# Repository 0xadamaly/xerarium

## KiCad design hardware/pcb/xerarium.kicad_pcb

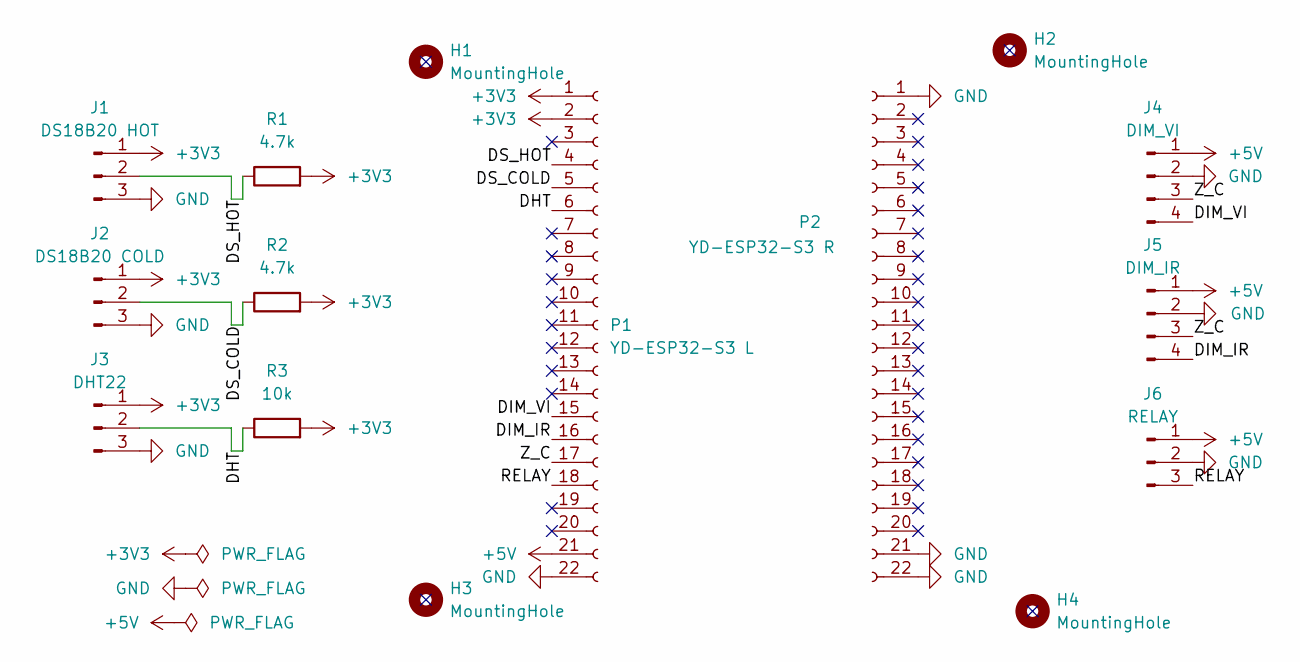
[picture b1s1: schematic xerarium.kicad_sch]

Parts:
H1, H2, H3, H4: MountingHole; MountingHole_3.2mm_M3
J1: DS18B20 HOT; JST_PH_S3B-PH-K_1x03_P2.00mm_Horizontal; MPN S3B-PH-K-S(LF)(SN)
J2: DS18B20 COLD; JST_PH_S3B-PH-K_1x03_P2.00mm_Horizontal; MPN S3B-PH-K-S(LF)(SN)
J3: DHT22; JST_PH_S3B-PH-K_1x03_P2.00mm_Horizontal; MPN S3B-PH-K-S(LF)(SN)
J4: DIM_VI; JST_PH_S4B-PH-K_1x04_P2.00mm_Horizontal; MPN S4B-PH-K-S(LF)(SN)
J5: DIM_IR; JST_PH_S4B-PH-K_1x04_P2.00mm_Horizontal; MPN S4B-PH-K-S(LF)(SN)
J6: RELAY; JST_PH_S3B-PH-K_1x03_P2.00mm_Horizontal; MPN S3B-PH-K-S(LF)(SN)
P1: YD-ESP32-S3 L; PinSocket_1x22_P2.54mm_Vertical; MPN SSW-122-01-T-S
P2: YD-ESP32-S3 R; PinSocket_1x22_P2.54mm_Vertical; MPN SSW-122-01-T-S
R1, R2: 4.7k; R_Axial_DIN0207_L6.3mm_D2.5mm_P10.16mm_Horizontal; MPN MFR-25FBF52-4K7
R3: 10k; R_Axial_DIN0207_L6.3mm_D2.5mm_P10.16mm_Horizontal; MPN MFR-25FBF52-10K

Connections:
+3V3: J1.1, J2.1, J3.1, P1.1, P1.2, R1.2, R2.2, R3.2
+5V: J4.1, J5.1, J6.1, P1.21
/DHT: J3.2, P1.6, R3.1
/DIM_IR: J5.4, P1.16
/DIM_VI: J4.4, P1.15
/DS_COLD: J2.2, P1.5, R2.1
/DS_HOT: J1.2, P1.4, R1.1
/RELAY: J6.3, P1.18
/Z_C: J4.3, J5.3, P1.17
GND: J1.3, J2.3, J3.3, J4.2, J5.2, J6.2, P1.22, P2.1, P2.21, P2.22

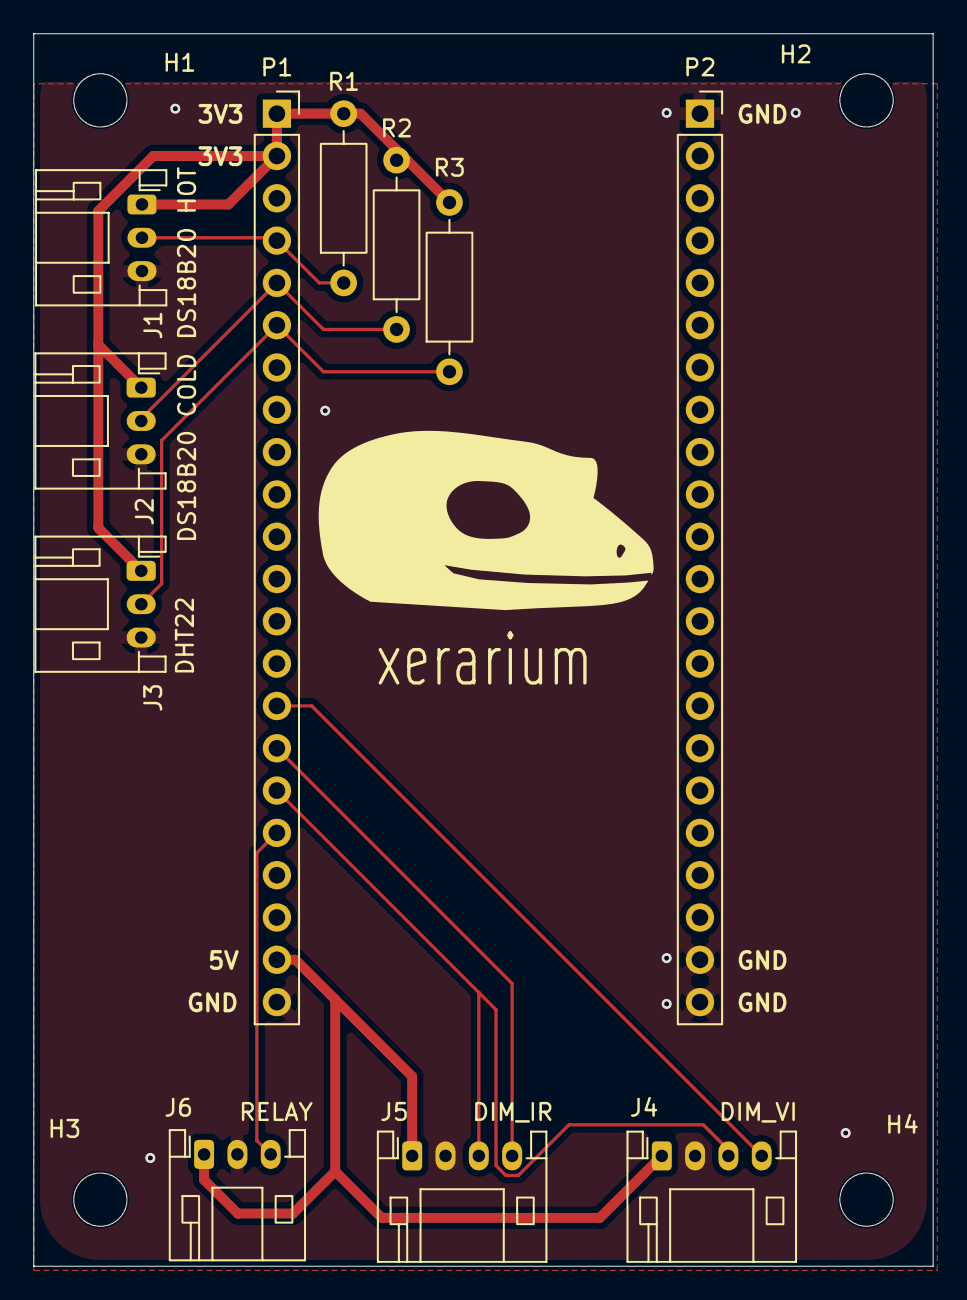
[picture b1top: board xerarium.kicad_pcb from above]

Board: 2 copper layers, 54.0 x 74.0 mm, 15 parts (0 on the bottom side), 10 nets.

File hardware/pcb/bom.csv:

Reference,Qty,Value,Footprint,MPN,Manufacturer,Chosen_Distributor,Datasheet,Validated,DNP,Notes
J1,1,DS18B20 HOT,JST_PH_S3B-PH-K_1x03_P2.00mm_Horizontal,S3B-PH-K-S(LF)(SN),JST,,,,,
J2,1,DS18B20 COLD,JST_PH_S3B-PH-K_1x03_P2.00mm_Horizontal,S3B-PH-K-S(LF)(SN),JST,,,,,
J3,1,DHT22,JST_PH_S3B-PH-K_1x03_P2.00mm_Horizontal,S3B-PH-K-S(LF)(SN),JST,,,,,
J4,1,DIM_VI,JST_PH_S4B-PH-K_1x04_P2.00mm_Horizontal,S4B-PH-K-S(LF)(SN),JST,,,,,
J5,1,DIM_IR,JST_PH_S4B-PH-K_1x04_P2.00mm_Horizontal,S4B-PH-K-S(LF)(SN),JST,,,,,
J6,1,RELAY,JST_PH_S3B-PH-K_1x03_P2.00mm_Horizontal,S3B-PH-K-S(LF)(SN),JST,,,,,
P1,1,YD-ESP32-S3 L,PinSocket_1x22_P2.54mm_Vertical,SSW-122-01-T-S,Samtec,,,,,1x22 2.54mm female socket strip — or SSW-140 cut to 22
P2,1,YD-ESP32-S3 R,PinSocket_1x22_P2.54mm_Vertical,SSW-122-01-T-S,Samtec,,,,,1x22 2.54mm female socket strip — or SSW-140 cut to 22
"R2,R1",2,4.7k,Axial_DIN0207_L6.3mm_D2.5mm_P10.16mm_Horizontal,MFR-25FBF52-4K7,Yageo,,,,,
R3,1,10k,Axial_DIN0207_L6.3mm_D2.5mm_P10.16mm_Horizontal,MFR-25FBF52-10K,Yageo,,,,,
